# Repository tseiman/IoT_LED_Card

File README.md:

# IoT LED Card

IoT card for Sierra Wireless MangOH (https://mangoh.io) boards and FX30 ready made IoT Device.
4 Controllable RGB LEDs. The RGB LEDs are driven via a 16 channel RGB controler PCA9685PW (https://www.nxp.com/docs/en/data-sheet/PCA9685.pdf). 
From this 16 channels 3 (RGB) x 4 LEDs = 12 Channels are used.
The IoT card uses the UART and a UART to I2C converter to communicate to the RGB controller.
UART to I2C conversion is done with SC18IM700 (https://www.nxp.com/docs/en/data-sheet/SC18IM700.pdf)

## Communicating to I2C via the SC18IM700 converter
The address of the RGB driver PCA9685PW is fixed wired to 80h (write) and 81h (read).
The communication via UART is in binary. The UART itself runs in default mode of the SC18IM799 UART<-->I2C converter which is 9600Baud 8N1, no flow control.
For each I2C start command a 53h is send, for a I2C stop a 50h is send.
An example communication to write:
```
0x53 0x80 0x02 0xfa 0x00 0x50 

0x53 --> I2C Start Condition (executed by SC18IM700)
0x80 --> This is the I2C address of the I2C slave
0x02 --> 2 bytes to write (length)
0xfa 0x00 --> the data bytes
0x50 --> let the UART<-->I2C converter SC18IM700 create a I2C stop condition
```

Another Example:

```
// This sets the read pointer to the first register (Register MODE1) 
// of the RGB driver by writing 1 byte (0x01) with the value 0x0.
0x53 0x80 0x01 0x00 0x50

// This reads one byte from the RGB drivers's first register 
0x53 0x81 0x01 0x50
```
Please follow the datasheets of the RGB driver's PCA9685PW and the datasheet of the UART to I2C converter SC18IM700 tightly as the communication with this IoT Card is fully based on it. 

## Example Initialisation
The UART to I2C converter is running with it power up default settings. It is possible to set e.g. baud rate - which is not done at the moment (but everybody who implements a driver or an Octave script is free to do).
However the RGB needs to be initilized (the commands are all documented in the PCA9685 datasheet):

```
						// This both lines reset all LED channels:
0x53 0x80 0x02 0xfa 0x00 0x50     		// addresses register ALL_LED_ON_L (0xfa)
0x53 0x80 0x03 0xfc 0x10 0x00 0x50		// addresses register ALL_LED_OFF_L (0xfc) 
						
0x53 0x80 0x02 0x01 0x10 0x50			// addressing MODE2 register (0x01). 
						// Due to the design of the LED driver 
						// with the LEDs (LEDs are directly connected 
						// to the driver without FETs) 
						// the logic is inverted. This logic negation 
						// can be configured in MODE2 
						// register of RGB driver. For this setup 
						// INVRT bit must be HIGH and 
						// OUTDRV bit must be LOW - see the PCA9685 
						// Rev.4 datasheet p.29, Table 12. for
						// further information

0x53 0x80 0x01 0x00 0x50 0x53 0x81 0x01 0x50	// this reads the first (0x00) MODE1 
						// register by first setting the read 
						// pointer to first (0x00) register 
						// and then read 1 byte. It should 
						// return 0x11.
						// as autoincrement of the register 
						// is disabled by default on power up
						// we can directly write now to 
						// MODE1 register:
0x53 0x80 0x02 0x00 0x31 0x50			// the value 0x31 in MODE1 register
						// which disables RESTART and enables 
						// Register Auto Increment Please 
						// see PCA9685 Rev.4 datasheet p.14, 
						// Table 5. 
						// for further information, the PWM 
						// oscilator is still off at this stage

0x53 0x80 0x02 0xFE 0x79 0x50			// This set the PRE_SCALE Register (0xfe) 
						// to 50hz (can be adapted to different freq.)

0x53 0x80 0x02 0x00 0x21 0x50			// Changes in MODE1 register from Low power 
						// mode (Oscilators=Off) to normal mode (Osc.=On)

/* now PCA9685 needs 500us to stabilize the oscilator */
                                    
0x53 0x80 0x02 0x00 0xa1 0x50			// after 500us the initialisation 
						// can be finalized. After that 
						// we switch in MODE1 register the restart 
						// Bit (0xa1) - after restart the PCA9685 
						// is operational
    
```

## Writing to LED channels

The LED Driver offers 16 channels. Each Channel can be individually controlled with PWM parameters (related to one central Oscilator). 
The time of the duty cycle period and it's offset to the Oscilator clock can be defined by various registers.
Each channel has a LED_OFF_H, LED_OFF_L and a LED_ON_H, LED_ON_L register. The Low (L) registers are 8bit, from the High register only 4 Bits are used so in total a range of 0-4095 can be achived.
In this example the OFF registers are always on 0x0 (please check the PCA9685 datasheet for more in depth information). 

An example to set the brightnes of one channel:

```
53 80 03 06 00 00 50    53 80 03 08 ff 0f 50  	// The LED0 channel (first LED, Red) 
						// the LED_OFF Register is at address 0x06
//  LED0_OFF to 0x0	 LED0_ON to 4095 (max)	// the LED0 channel LED_ON Register is at 0x08
						// This sequence sets LED0 channel 
						// to maximum brightness.
						// Note that the LOW byte is transfered 
						// first - then the HIGH byte

```

## LED Channel Mapping:

| LED on IoT Card | Channel | Channel on PCA9685 | PCA9685 LED_OFF Addr. | PCA9685 LED_ON Addr. |
|:---------------:|:-------:|:------------------:|:---------------------:|:--------------------:|
| 0		  | R	    | 0			 | 0x06			 | 0x08			|
| 0		  | G	    | 1			 | 0x0a			 | 0x0c			|
| 0		  | B	    | 2			 | 0x0e			 | 0x10			|
| 		  | 	    | 			 | 			 | 			|
| 1		  | R	    | 3			 | 0x12			 | 0x14			|
| 1		  | G	    | 4			 | 0x16			 | 0x18			|
| 1		  | B	    | 5			 | 0x1a			 | 0x1c			|
| 		  | 	    | 			 | 			 | 			|
| 2		  | R	    | 6			 | 0x1e			 | 0x20			|
| 2		  | G	    | 7			 | 0x22			 | 0x24			|
| 2		  | B	    | 8			 | 0x26			 | 0x28			|
| 		  | 	    | 			 | 			 | 			|
| 3		  | R	    | 9			 | 0x2a			 | 0x2c			|
| 3		  | G	    | 10		 | 0x2e			 | 0x30			|
| 3		  | B	    | 12		 | 0x32			 | 0x34			|

## Octave Example Code

### Initialisation 

Initialisation, Requires Counter Resource enabled, the Edge Action triggers on a Counter Observation 

```javascript
function(event) {

  if(event.value === 2) { // Huston we have a startup, triggering the first initialisation
    return {
      "dh://lcd/txt1": ["Init I2C"], 
      "vr://LED_I2C_is_init": [ false ], 
      "vr://ledI2CInitStep": [ 3 ], 
    }
  }

  var initDone = Datahub.read("/virtual/LED_I2C_is_init/value",0).value;

  if(initDone) {  // we're initialized don't do anything further
    return {"dh://lcd/txt1": ["no init"] }
  }
  var initStepValue = Datahub.read("/virtual/ledI2CInitStep/value",0).value; // if init is needed reading the counter value when init needs to be started

  var pca9685Init1 = { "data":  [
    0x53, 0x80, 0x02, 0xfa, 0x00, 0x50,
    0x53, 0x80, 0x03, 0xfc, 0x10, 0x00, 0x50,
    0x53, 0x80, 0x02, 0x01, 0x10, 0x50,
    0x53, 0x80, 0x01, 0x00, 0x50, 0x53, 0x81, 0x01, 0x50,
    0x53, 0x80, 0x02, 0x00, 0x31, 0x50,
    0x53, 0x80, 0x02, 0xFE, 0x79, 0x50,
    0x53, 0x80, 0x02, 0x00, 0x21, 0x50
  ]};

 var pca9685Init2 = { "data":  [
    0x53, 0x80, 0x02, 0x00, 0xa1, 0x50,
    0x53, 0x80, 0x03, 0x06, 0x00, 0x00, 0x50,    0x53, 0x80, 0x03, 0x08, 0x00, 0x00, 0x50,  
    0x53, 0x80, 0x03, 0x0a, 0x00, 0x00, 0x50,    0x53, 0x80, 0x03, 0x0c, 0x00, 0x00, 0x50,  
    0x53, 0x80, 0x03, 0x0e, 0x00, 0x00, 0x50,    0x53, 0x80, 0x03, 0x10, 0x00, 0x00, 0x50,  
  ]};

  if(event.value === initStepValue) { // Huston we have a startup, sending the first initialisation
    return {
      "dh://lcd/txt1": ["Running init seq"],                                                                              
      "dh://usp/write": [pca9685Init1],
    }

  }
  if(event.value === (initStepValue + 1)) { // actually we need to wait 500us until the PCM clock of the PCA9685 stabilizes - then we finalize, here we wait until the next couter incement (a bit longer than 500us) 
    return {
      "dh://lcd/txt1": ["DONE Running init seq"],                                                                              
      "dh://usp/write": [pca9685Init2],
      "vr://LED_I2C_is_init": [ true ], 
    }

  }
  
  return {  
     "dh://lcd/txt1": ["wait for init:" + event.value] 

  }

}

```

Writing brightness information:

```javascript
function(event) {

	if(event.value.type === "reset") {
      var initStepValue = Datahub.read("/util/counter/value",0).value + 1; 
		
      return {
        "dh://lcd/txt1": ["Init I2C"], 
        "vr://LED_I2C_is_init": [ false ], 
        "vr://ledI2CInitStep": [ initStepValue ], 
      }
  	}

	if(event.value.type === "setled") {

      var data = new Array();

	    if(event.value.hasOwnProperty("LED_0")){
	        var ledVal = event.value.LED_0;
	        if(ledVal.hasOwnProperty("R")){
	            var LEDvalue = ledVal.R;
	            var LED_Red_H = (LEDvalue & 0x0fff) >> 8;
	            var LED_Red_L = (LEDvalue & 0xff);
	            var ledCtrl = [0x53, 0x80, 0x03, 0x06, 0x00, 0x00, 0x50, 0x53, 0x80, 0x03, 0x08, LED_Red_L,   LED_Red_H,   0x50];
	            data.push.apply(data,ledCtrl);
	        }
	        if(ledVal.hasOwnProperty("G")){
	            var LEDvalue = ledVal.G;
	            var LED_Green_H = (LEDvalue & 0x0fff) >> 8;
	            var LED_Green_L = (LEDvalue & 0xff);
	        
	            var ledCtrl = [0x53, 0x80, 0x03, 0x0a, 0x00, 0x00, 0x50,    0x53, 0x80, 0x03, 0x0c, LED_Green_L, LED_Green_H, 0x50];
	            data.push.apply(data,ledCtrl);
	        }
	        if(ledVal.hasOwnProperty("B")){

	            var LEDvalue = ledVal.B;
	            var LED_Blue_H = (LEDvalue & 0x0fff) >> 8;
	            var LED_Blue_L = (LEDvalue & 0xff);
	        
	            var ledCtrl = [ 0x53, 0x80, 0x03, 0x0e, 0x00, 0x00, 0x50,    0x53, 0x80, 0x03, 0x10, LED_Blue_L,  LED_Blue_H,  0x50];
	            data.push.apply(data,ledCtrl);
	        }
	    }

	    if(event.value.hasOwnProperty("LED_1")){
	        var ledVal = event.value.LED_1;
	        if(ledVal.hasOwnProperty("R")){
	            var LEDvalue = ledVal.R;
	            var LED_Red_H = (LEDvalue & 0x0fff) >> 8;
	            var LED_Red_L = (LEDvalue & 0xff);
	            var ledCtrl = [0x53, 0x80, 0x03, 0x12, 0x00, 0x00, 0x50, 0x53, 0x80, 0x03, 0x14, LED_Red_L,   LED_Red_H,   0x50];
	            data.push.apply(data,ledCtrl);
	        }
	        if(ledVal.hasOwnProperty("G")){
	            var LEDvalue = ledVal.G;
	            var LED_Green_H = (LEDvalue & 0x0fff) >> 8;
	            var LED_Green_L = (LEDvalue & 0xff);
	        
	            var ledCtrl = [0x53, 0x80, 0x03, 0x16, 0x00, 0x00, 0x50,    0x53, 0x80, 0x03, 0x18, LED_Green_L, LED_Green_H, 0x50];
	            data.push.apply(data,ledCtrl);
	        }
	        if(ledVal.hasOwnProperty("B")){

	            var LEDvalue = ledVal.B;
	            var LED_Blue_H = (LEDvalue & 0x0fff) >> 8;
	            var LED_Blue_L = (LEDvalue & 0xff);
	        
	            var ledCtrl = [ 0x53, 0x80, 0x03, 0x1a, 0x00, 0x00, 0x50,    0x53, 0x80, 0x03, 0x1c, LED_Blue_L,  LED_Blue_H,  0x50];
	            data.push.apply(data,ledCtrl);
	        }
	    }

		if(event.value.hasOwnProperty("LED_2")){
			var ledVal = event.value.LED_2;
			if(ledVal.hasOwnProperty("R")){
			    var LEDvalue = ledVal.R;
			    var LED_Red_H = (LEDvalue & 0x0fff) >> 8;
			    var LED_Red_L = (LEDvalue & 0xff);
			    var ledCtrl = [0x53, 0x80, 0x03, 0x1e, 0x00, 0x00, 0x50, 0x53, 0x80, 0x03, 0x20, LED_Red_L,   LED_Red_H,   0x50];
			    data.push.apply(data,ledCtrl);
			}
			if(ledVal.hasOwnProperty("G")){
			    var LEDvalue = ledVal.G;
			    var LED_Green_H = (LEDvalue & 0x0fff) >> 8;
			    var LED_Green_L = (LEDvalue & 0xff);

			    var ledCtrl = [0x53, 0x80, 0x03, 0x22, 0x00, 0x00, 0x50,    0x53, 0x80, 0x03, 0x24, LED_Green_L, LED_Green_H, 0x50];
			    data.push.apply(data,ledCtrl);
			}
			if(ledVal.hasOwnProperty("B")){

			    var LEDvalue = ledVal.B;
			    var LED_Blue_H = (LEDvalue & 0x0fff) >> 8;
			    var LED_Blue_L = (LEDvalue & 0xff);

			    var ledCtrl = [ 0x53, 0x80, 0x03, 0x26, 0x00, 0x00, 0x50,    0x53, 0x80, 0x03, 0x28, LED_Blue_L,  LED_Blue_H,  0x50];
			    data.push.apply(data,ledCtrl);
			}
		}

		if(event.value.hasOwnProperty("LED_3")){
			var ledVal = event.value.LED_3;
			if(ledVal.hasOwnProperty("R")){
			    var LEDvalue = ledVal.R;
			    var LED_Red_H = (LEDvalue & 0x0fff) >> 8;
			    var LED_Red_L = (LEDvalue & 0xff);
			    var ledCtrl = [0x53, 0x80, 0x03, 0x2a, 0x00, 0x00, 0x50, 0x53, 0x80, 0x03, 0x2c, LED_Red_L,   LED_Red_H,   0x50];
			    data.push.apply(data,ledCtrl);
			}
			if(ledVal.hasOwnProperty("G")){
			    var LEDvalue = ledVal.G;
			    var LED_Green_H = (LEDvalue & 0x0fff) >> 8;
			    var LED_Green_L = (LEDvalue & 0xff);

			    var ledCtrl = [0x53, 0x80, 0x03, 0x2e, 0x00, 0x00, 0x50,    0x53, 0x80, 0x03, 0x30, LED_Green_L, LED_Green_H, 0x50];
			    data.push.apply(data,ledCtrl);
			}
			if(ledVal.hasOwnProperty("B")){

			    var LEDvalue = ledVal.B;
			    var LED_Blue_H = (LEDvalue & 0x0fff) >> 8;
			    var LED_Blue_L = (LEDvalue & 0xff);

			    var ledCtrl = [ 0x53, 0x80, 0x03, 0x32, 0x00, 0x00, 0x50,    0x53, 0x80, 0x03, 0x34, LED_Blue_L,  LED_Blue_H,  0x50];
			    data.push.apply(data,ledCtrl);
			}
		}

        if(data.length >= 14) {
          return {
            "dh://lcd/txt1": ["Write to LED " + data.length + " bytes"], 
            "dh://usp/write": [{ "data": data }],
          }
    	}

  	}

}

```

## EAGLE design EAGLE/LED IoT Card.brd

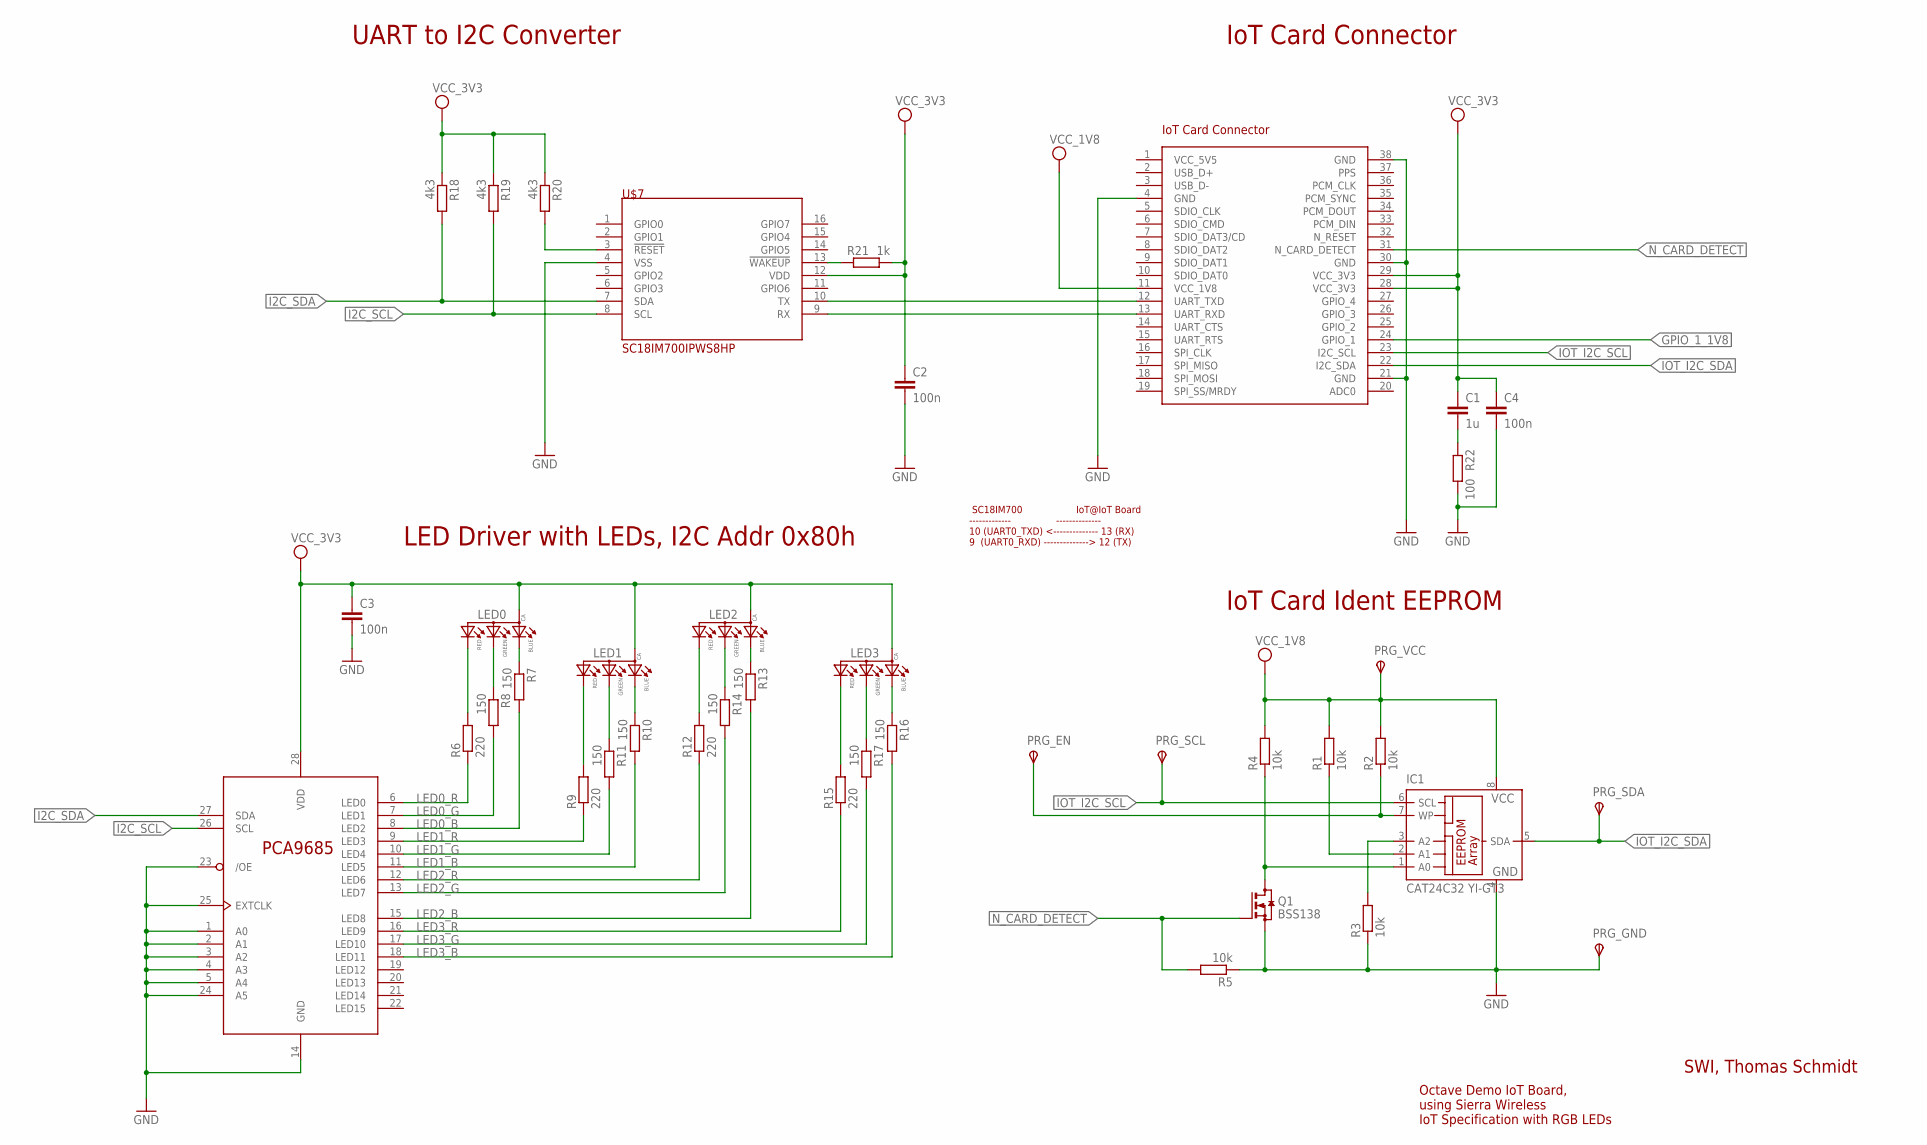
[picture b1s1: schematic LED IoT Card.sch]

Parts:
C1: 1u; C0805K
C2, C3, C4: 100n; C0603K
IC1: CAT24C32 YI-GT3; TSSOP8
LED0, LED1, LED2, LED3: 0.13_RGB_LEDPLCC; P-LCC-4-3
PRG_EN: TPSB1,27; B1,27
PRG_GND: TPSB1,27; B1,27
PRG_SCL: TPSB1,27; B1,27
PRG_SDA: TPSB1,27; B1,27
PRG_VCC: TPSB1,27; B1,27
Q1: BSS138; SOT23
R1, R2, R3, R4, R5: 10k; R0402
R6, R9, R12, R15: 220; R0402
R7, R8, R10, R11, R13, R14, R16, R17: 150; R0402
R18, R19, R20: 4k3; R0402
R21: 1k; R0402
R22: 100; R0402
U$1: IOTLONG; IOT_LONG
U$2: PCA9685PW; TSSOP28
U$7: SC18IM700IPWS8HP; TSSOP16

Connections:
EEPROM_A0: IC1.1 (A0), Q1.3 (D), R4.1
EEPROM_A1: IC1.2 (A1), R1.1
EEPROM_A2: IC1.3 (A2), R3.2
EEPROM_WP: IC1.7 (WP), PRG_EN.TP, R2.1
GND: C2.2, C3.2, C4.2, IC1.4 (GND), PRG_GND.TP, Q1.2 (S), R3.1, R5.1, R22.2, U$1.4 (GND), U$1.21 (GND), U$1.30 (GND), U$1.38 (GND), U$2.1 (A0), U$2.2 (A1), U$2.3 (A2), U$2.4 (A3), U$2.5 (A4), U$2.14 (GND), U$2.23 (/OE), U$2.24 (A5), U$2.25 (EXTCLK), U$7.4 (VSS)
GPIO_1_1V8: U$1.24 (GPIO_1)
I2C_SCL: R19.2, U$2.26 (SCL), U$7.8 (SCL)
I2C_SDA: R18.2, U$2.27 (SDA), U$7.7 (SDA)
IOT_I2C_SCL: IC1.6 (SCL), PRG_SCL.TP, U$1.23 (I2C_SCL)
IOT_I2C_SDA: IC1.5 (SDA), PRG_SDA.TP, U$1.22 (I2C_SDA)
LED0_B: R7.2, U$2.8 (LED2)
LED0_G: R8.2, U$2.7 (LED1)
LED0_R: R6.1, U$2.6 (LED0)
LED1_B: R10.2, U$2.11 (LED5)
LED1_G: R11.2, U$2.10 (LED4)
LED1_R: R9.1, U$2.9 (LED3)
LED2_B: R13.2, U$2.15 (LED8)
LED2_G: R14.2, U$2.13 (LED7)
LED2_R: R12.1, U$2.12 (LED6)
LED3_B: R16.2, U$2.18 (LED11)
LED3_G: R17.2, U$2.17 (LED10)
LED3_R: R15.1, U$2.16 (LED9)
unnamed: R20.2, U$7.3 (!RESET)
unnamed: R21.1, U$7.13 (!WAKEUP)
unnamed: C1.2, R22.1
N_CARD_DETECT: Q1.1 (G), R5.2, U$1.31 (N_CARD_DETECT)
RES_LED0_B: LED0.3 (BLUE), R7.1
RES_LED0_G: LED0.2 (GREEN), R8.1
RES_LED0_R: LED0.1 (RED), R6.2
RES_LED1_B: LED1.3 (BLUE), R10.1
RES_LED1_G: LED1.2 (GREEN), R11.1
RES_LED1_R: LED1.1 (RED), R9.2
RES_LED2_B: LED2.3 (BLUE), R13.1
RES_LED2_G: LED2.2 (GREEN), R14.1
RES_LED2_R: LED2.1 (RED), R12.2
RES_LED3_B: LED3.3 (BLUE), R16.1
RES_LED3_G: LED3.2 (GREEN), R17.1
RES_LED3_R: LED3.1 (RED), R15.2
SC18IM-RX_IOT-TX: U$1.12 (UART_TXD), U$7.10 (TX)
SC18IM-TX_IOT-RX: U$1.13 (UART_RXD), U$7.9 (RX)
VCC_1V8: IC1.8 (VCC), PRG_VCC.TP, R1.2, R2.2, R4.2, U$1.11 (VCC_1V8)
VCC_3V3: C1.1, C2.1, C3.1, C4.1, LED0.4 (ANODE), LED1.4 (ANODE), LED2.4 (ANODE), LED3.4 (ANODE), R18.1, R19.1, R20.1, R21.2, U$1.28 (VCC_3V3), U$1.29 (VCC_3V3), U$2.28 (VDD), U$7.12 (VDD)
VCC_5V5: U$1.1 (VCC_5V5)

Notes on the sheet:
IoT Card Ident EEPROM
SWI, Thomas Schmidt
Octave Demo IoT Board, using Sierra Wireless IoT Specification with RGB LEDs
SC18IM700 IoT@IoT Board ------------- -------------- 10 (UART0_TXD) <-------------- 13 (RX) 9 (UART0_RXD) --------------> 12 (TX)
LED Driver with LEDs, I2C Addr 0x80h
UART to I2C Converter
IoT Card Connector

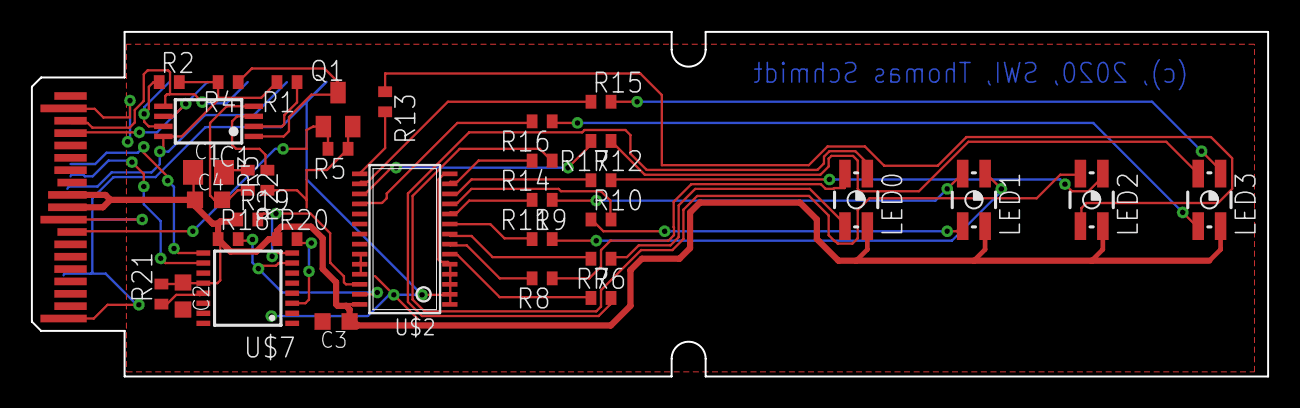
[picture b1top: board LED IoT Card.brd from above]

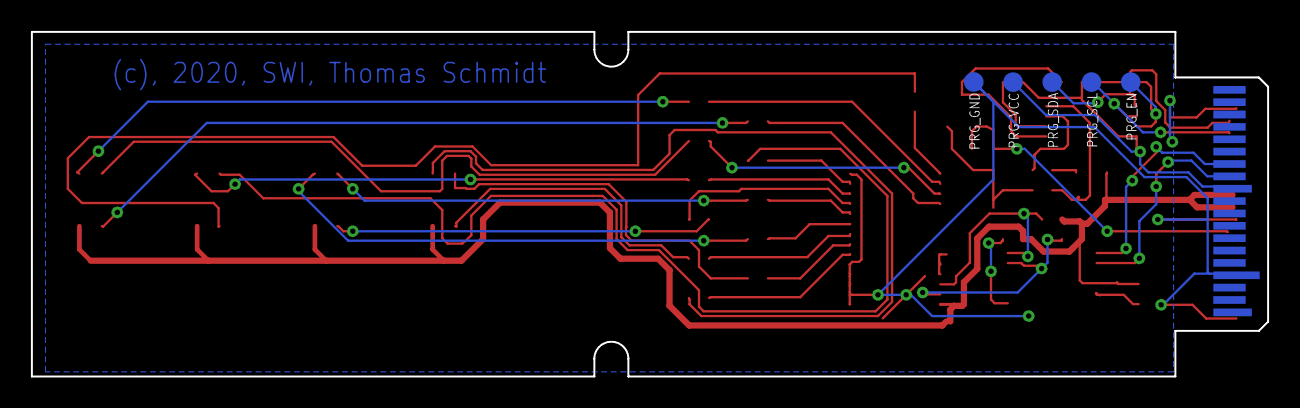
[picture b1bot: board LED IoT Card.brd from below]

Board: 2 copper layers, 80.0 x 22.3 mm, 40 parts (5 on the bottom side), 41 nets.

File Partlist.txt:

Partlist

Exported from LED IoT Card.sch at 29.09.20 15:35

EAGLE Version 9.6.2 Copyright (c) 1988-2020 Autodesk, Inc.

Assembly variant: 

Part     Value                       Device           Package   Library                 Sheet

C1       1u                          C-EUC0805K       C0805K    rcl                     1
C2       100n                        C-EUC0603K       C0603K    rcl                     1
C3       100n                        C-EUC0603K       C0603K    rcl                     1
C4       100n                        C-EUC0603K       C0603K    rcl                     1
IC1      CAT24C32             YI-GT3 24C64ST          TSSOP8    microchip               1
LED0                                 0.13_RGB_LEDPLCC P-LCC-4-3 LEDs                    1
LED1                                 0.13_RGB_LEDPLCC P-LCC-4-3 LEDs                    1
LED2                                 0.13_RGB_LEDPLCC P-LCC-4-3 LEDs                    1
LED3                                 0.13_RGB_LEDPLCC P-LCC-4-3 LEDs                    1
Q1       BSS138                      BSS123           SOT23     transistor-small-signal 1

R1       10k                         R-EU_R0402       R0402     rcl                     1
R2       10k                         R-EU_R0402       R0402     rcl                     1
R3       10k                         R-EU_R0402       R0402     rcl                     1
R4       10k                         R-EU_R0402       R0402     rcl                     1
R5       10k                         R-EU_R0402       R0402     rcl                     1

R6       220                         R-EU_R0402       R0402     rcl                     1
R9       220                         R-EU_R0402       R0402     rcl                     1
R12      220                         R-EU_R0402       R0402     rcl                     1
R15      220                         R-EU_R0402       R0402     rcl                     1

R7       150                         R-EU_R0402       R0402     rcl                     1
R8       150                         R-EU_R0402       R0402     rcl                     1
R10      150                         R-EU_R0402       R0402     rcl                     1
R11      150                         R-EU_R0402       R0402     rcl                     1
R13      150                         R-EU_R0402       R0402     rcl                     1
R14      150                         R-EU_R0402       R0402     rcl                     1
R16      150                         R-EU_R0402       R0402     rcl                     1
R17      150                         R-EU_R0402       R0402     rcl                     1

R18      4k3                         R-EU_R0402       R0402     rcl                     1
R19      4k3                         R-EU_R0402       R0402     rcl                     1
R20      4k3                         R-EU_R0402       R0402     rcl                     1

R21      1k                          R-EU_R0402       R0402     rcl                     1

R22      100                         R-EU_R0402       R0402     rcl                     1


U$2      PCA9685PW                   PCA9685PW        TSSOP28   i2c-led-controller      1
U$7      SC18IM700IPWS8HP            SC18IM700IPWS8HP TSSOP16   SC18IM700IPW            1


-------------


1x           1u                          C-EUC0805K       C0805K    rcl                     1           	OK R - Conf
3x           100n                        C-EUC0603K       C0603K    rcl                     1 				OK R - Conf
4x		                                 0.13_RGB_LEDPLCC P-LCC-4-3 LEDs                    1       6x		OK R - Conf
1x 		     CAT24C32             YI-GT3 24C64ST          TSSOP8    microchip               1 				OK D - Conf
1x		     PCA9685PW                   PCA9685PW        TSSOP28   i2c-led-controller      1       4x		OK D - Conf
1x		     SC18IM700IPWS8HP            SC18IM700IPWS8HP TSSOP16   SC18IM700IPW            1       4x		OK D - Conf
1x			 BSS138                      BSS123           SOT23     transistor-small-signal 1 				OK D - Conf
5x 		     10k                         R-EU_R0402       R0402     rcl                     1    			OK R - Conf
4x		     220                         R-EU_R0402       R0402     rcl                     1   			OK R - Conf
8x       	 150                         R-EU_R0402       R0402     rcl                     1   			OK R - Conf
3x			 4k3                         R-EU_R0402       R0402     rcl                     1 				OK R - Conf
1x			 1k                          R-EU_R0402       R0402     rcl                     1 				OK R - Conf
1x			 100                         R-EU_R0402       R0402     rcl                     1 				OK R - Conf

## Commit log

2020-10-14 initial commit with files
2020-10-14 corrections on readme
2020-10-14 updated the board image
2020-10-14 added eeprom folder
2020-10-14 minor eeprom/REadme corrections
2020-10-15 added card picture
2020-10-15 correctd board picture
2020-10-15 minor corrections
2020-10-15 added second picture
2020-10-15 Update LICENSE

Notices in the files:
parts and their libraries:
LEDs: Licensing: Creative Commons ShareAlike 4.0 International - https://creativecommons.org/licenses/by-sa/4.0
